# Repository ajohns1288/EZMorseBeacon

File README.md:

# EZMorseBeacon
This program is for Arduino type microcontrollers and is designed to act as a beacon when paired with a radio.

It does this by outputing morse code on a PWM pin and keying PTT on another pin. This way, you can use it as a beacon, fox, etc. Please ensure your hardware design prevents damage to the radio or micro. It is strongly recommended the outputs are isolated from the radio by means of an optocoupler (PTT) or isolation/blocking capacitor (Audio). A low pass filter (capacitor between pin and ground) is recommended on the audio line to reduce the higher harmonics of the square wave.

Also included in the hardware folder is a KiCad project of a 3.3V coin cell powered AtTiny85 PCB that can be used as the hardware portion of this project. I have not built it yet so I cannot guarantee it works.

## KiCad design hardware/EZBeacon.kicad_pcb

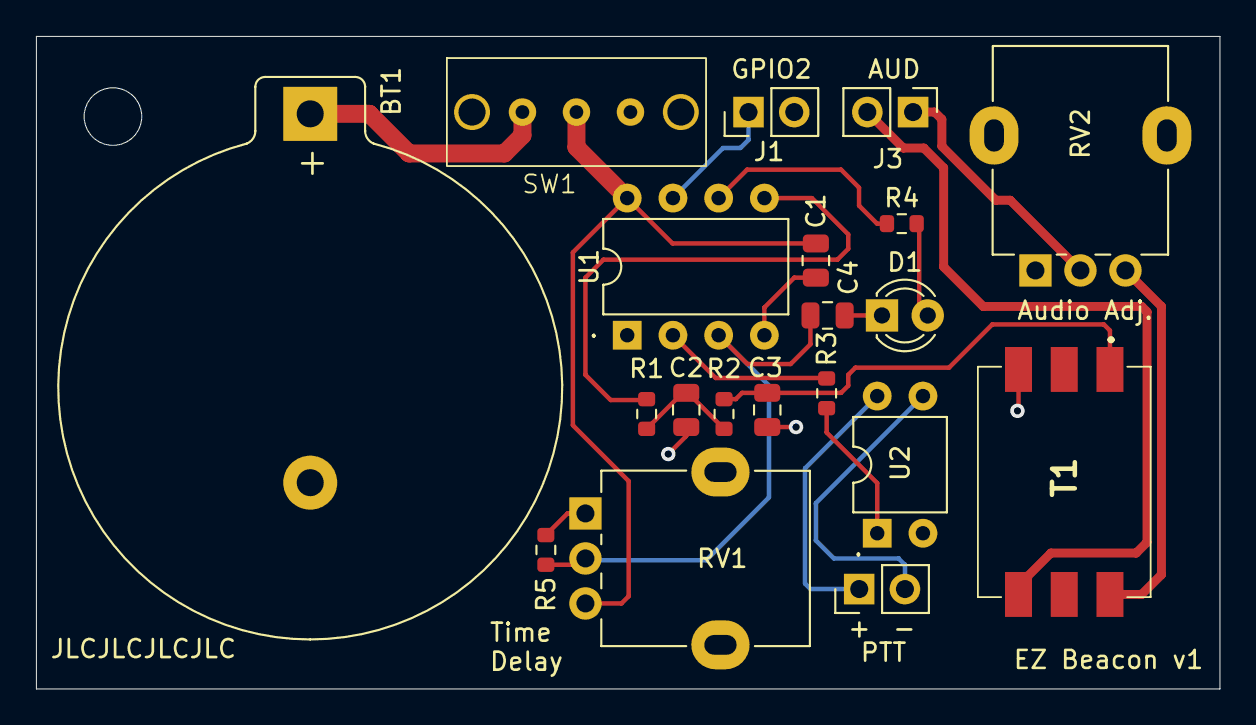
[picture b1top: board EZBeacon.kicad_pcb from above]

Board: 2 copper layers, 65.8 x 36.2 mm, 20 parts (0 on the bottom side), 17 nets.

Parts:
BT1: Battery_Cell; BatteryHolder_Keystone_106_1x20mm
C1, C4: 1u; C_0805_2012Metric
C2, C3: 20u; C_0805_2012Metric
D1: LED; LED_D3.0mm
J1, J2, J3: Conn_01x02_Socket; PinHeader_1x02_P2.54mm_Vertical
R1, R3, R4: 100; R_0603_1608Metric
R2: 80; R_0603_1608Metric
R5: 100k; R_0603_1608Metric
RV1, RV2: R_Potentiometer; Potentiometer_Alpha_RD901F-40-00D_Single_Vertical
SW1: SW_Push; SLW-121586
T1: SM-LP-5001E; SMLP5001E
U1: ATtiny85-20P; DIP-8_W7.62mm
U2: PC817; DIP-4_W7.62mm

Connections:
+3.3V: C1.1, RV1.3, SW1.2, U1.8 (VCC)
ADC2: C4.1, R5.1, RV1.2, U1.3 (XTAL2/PB4)
CIPO: R4.1, U1.6 (PB1)
COPI: R1.1, U1.5 (AREF/PB0)
D2: J1.1, U1.7 (PB2)
D3: R3.1, U1.2 (XTAL1/PB3)
GND: BT1.2 (-), C1.2, C2.2, C3.2, C4.2, D1.1 (K), J1.2, R5.2, RV1.1, T1.3, U1.4 (GND), U2.2
unnamed: BT1.1 (+), SW1.1
unnamed: C2.1, R1.2, R2.1
unnamed: C3.1, R2.2, T1.1
unnamed: D1.2 (A), R4.2
unnamed: J2.1, U2.4
unnamed: J2.2, U2.3
unnamed: J3.1, RV2.2
unnamed: J3.2, T1.4
unnamed: R3.2, U2.1
unnamed: RV2.3, T1.6

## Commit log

2024-03-09 Create EZMorseBeacon
